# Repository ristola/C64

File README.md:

# C64 Development Workspace

Four related but independent hardware/software projects.

## Projects

- **[`hello/`](hello/README.md)** — SHACKMATE: a working 13-bank EasyFlash BASIC+ extension cartridge for the C64, plus a planned custom flash-based cartridge/expansion-platform PCB that supersedes it, and a Magic Desk-format test build for an already-owned real-hardware bring-up board. The most developed project here; see its own README and `docs/` for full detail.
- **[`eprom-reader/`](eprom-reader/README.md)** — reads 27C64 through 27C512 EPROMs and stores the dump to disk. Scaffolding only, no design work started.
- **[`eeprom-writer/`](eeprom-writer/README.md)** — loads a 27CXX ROM binary and writes it to 27SF256-series EEPROMs. Scaffolding only, no design work started.
- **[`programmer-cartridge/`](programmer-cartridge/README.md)** — a C64 cartridge that programs other cartridges: a ZIF socket for loose EPROM/EEPROM chips plus a second socket for in-circuit programming a companion barebones (surface-mount, non-socketed) release cartridge, with all read/write/backup/clone/load tooling running on the C64 itself. Concept stage, no design work started.

## Why these are grouped together

`eprom-reader/`, `eeprom-writer/`, and `programmer-cartridge/` all exist to support hardware bring-up and eventual distribution for `hello/`'s planned custom board and its release cartridges — dumping/archiving existing EPROM-based cartridges, burning built ROM images during development, and (via `programmer-cartridge/`) eventually producing cheap, mass-producible release hardware. They're independent projects (own toolchains, own hardware, own timelines) but share that practical relationship, and `programmer-cartridge/`'s on-device software overlaps directly with `hello/`'s stubbed Bank 9 (`FLASHERASE`/`FLASHLOAD`/`FLASHVERIFY`) — the same flash erase/write/verify sequence serves both.

`EasyFlash-AppSupport.pdf` / `EasyFlash-ProgRef.pdf` are the real EasyFlash reference docs, kept here for cross-checking `hello/`'s hardware-platform design (GAME/EXROM behavior, register semantics) against something authoritative.

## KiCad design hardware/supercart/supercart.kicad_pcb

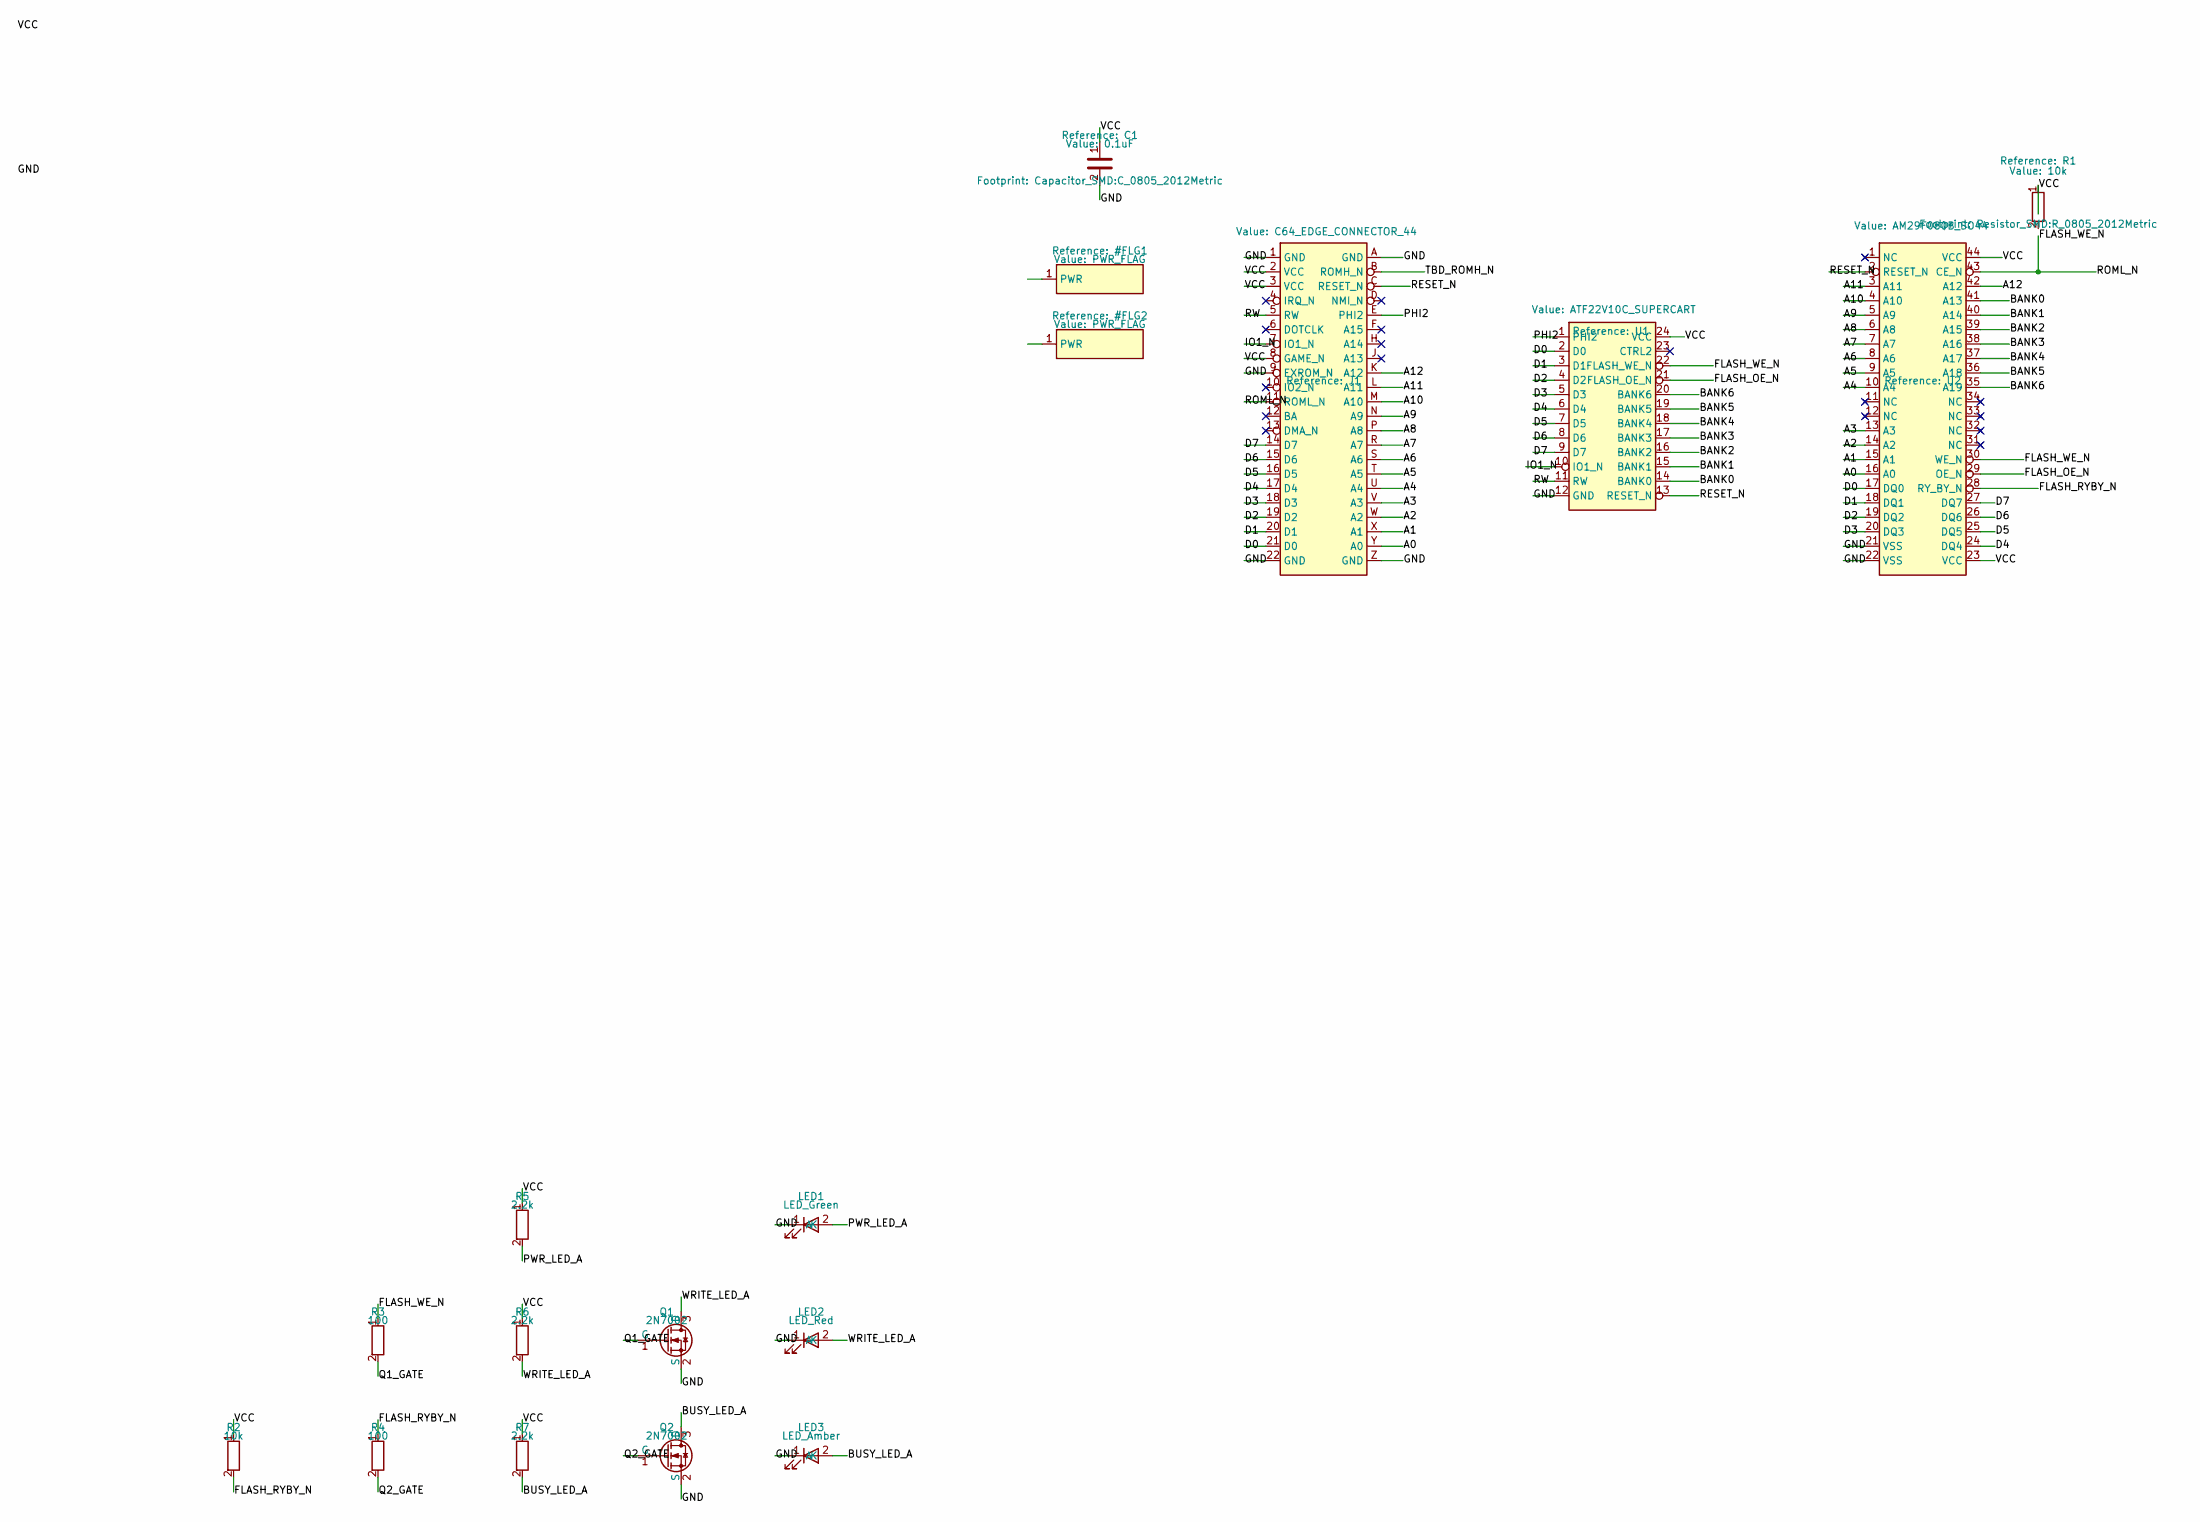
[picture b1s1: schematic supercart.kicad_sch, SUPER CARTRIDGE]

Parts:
C1: 0.1uF; C_0805_2012Metric
J1: C64_EDGE_CONNECTOR_44
LED1: LED_Green; LED_0805_2012Metric
LED2: LED_Red; LED_0805_2012Metric
LED3: LED_Amber; LED_0805_2012Metric
Q1, Q2: 2N7002; SOT-23
R1, R2: 10k; R_0805_2012Metric
R3, R4: 100; R_0805_2012Metric
R5, R6, R7: 2.2k; R_0805_2012Metric
U1: ATF22V10C_SUPERCART
U2: AM29F080B_SO44

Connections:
A0: J1.Y (A0), U2.16 (A0)
A1: J1.X (A1), U2.15 (A1)
A2: J1.W (A2), U2.14 (A2)
A3: J1.V (A3), U2.13 (A3)
A4: J1.U (A4), U2.10 (A4)
A5: J1.T (A5), U2.9 (A5)
A6: J1.S (A6), U2.8 (A6)
A7: J1.R (A7), U2.7 (A7)
A8: J1.P (A8), U2.6 (A8)
A9: J1.N (A9), U2.5 (A9)
A10: J1.M (A10), U2.4 (A10)
A11: J1.L (A11), U2.3 (A11)
A12: J1.K (A12), U2.42 (A12)
BANK0: U1.14 (BANK0), U2.41 (A13)
BANK1: U1.15 (BANK1), U2.40 (A14)
BANK2: U1.16 (BANK2), U2.39 (A15)
BANK3: U1.17 (BANK3), U2.38 (A16)
BANK4: U1.18 (BANK4), U2.37 (A17)
BANK5: U1.19 (BANK5), U2.36 (A18)
BANK6: U1.20 (BANK6), U2.35 (A19)
BUSY_LED_A: LED3.2 (A), Q2.3 (D), R7.2
D0: J1.21 (D0), U1.2 (D0), U2.17 (DQ0)
D1: J1.20 (D1), U1.3 (D1), U2.18 (DQ1)
D2: J1.19 (D2), U1.4 (D2), U2.19 (DQ2)
D3: J1.18 (D3), U1.5 (D3), U2.20 (DQ3)
D4: J1.17 (D4), U1.6 (D4), U2.24 (DQ4)
D5: J1.16 (D5), U1.7 (D5), U2.25 (DQ5)
D6: J1.15 (D6), U1.8 (D6), U2.26 (DQ6)
D7: J1.14 (D7), U1.9 (D7), U2.27 (DQ7)
FLASH_OE_N: U1.21 (FLASH_OE_N), U2.29 (OE_N)
FLASH_RYBY_N: R2.2, R4.1, U2.28 (RY_BY_N)
GND: C1.2, J1.1 (GND), J1.9 (EXROM_N), J1.22 (GND), J1.A (GND), J1.Z (GND), LED1.1 (K), LED2.1 (K), LED3.1 (K), Q1.2 (S), Q2.2 (S), U1.12 (GND), U2.21 (VSS), U2.22 (VSS); also elsewhere on the board
IO1_N: J1.7 (IO1_N), U1.10 (IO1_N)
PHI2: J1.E (PHI2), U1.1 (PHI2)
PWR_LED_A: LED1.2 (A), R5.2
Q1_GATE: Q1.1 (G), R3.2
Q2_GATE: Q2.1 (G), R4.2
RESET_N: J1.C (RESET_N), U1.13 (RESET_N), U2.2 (RESET_N)
RW: J1.5 (RW), U1.11 (RW)
TBD_ROMH_N: J1.B (ROMH_N)
VCC: C1.1, J1.2 (VCC), J1.3 (VCC), J1.8 (GAME_N), R1.1, R2.1, R5.1, R6.1, R7.1, U1.24 (VCC), U2.23 (VCC), U2.44 (VCC); also elsewhere on the board
WRITE_LED_A: LED2.2 (A), Q1.3 (D), R6.2

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
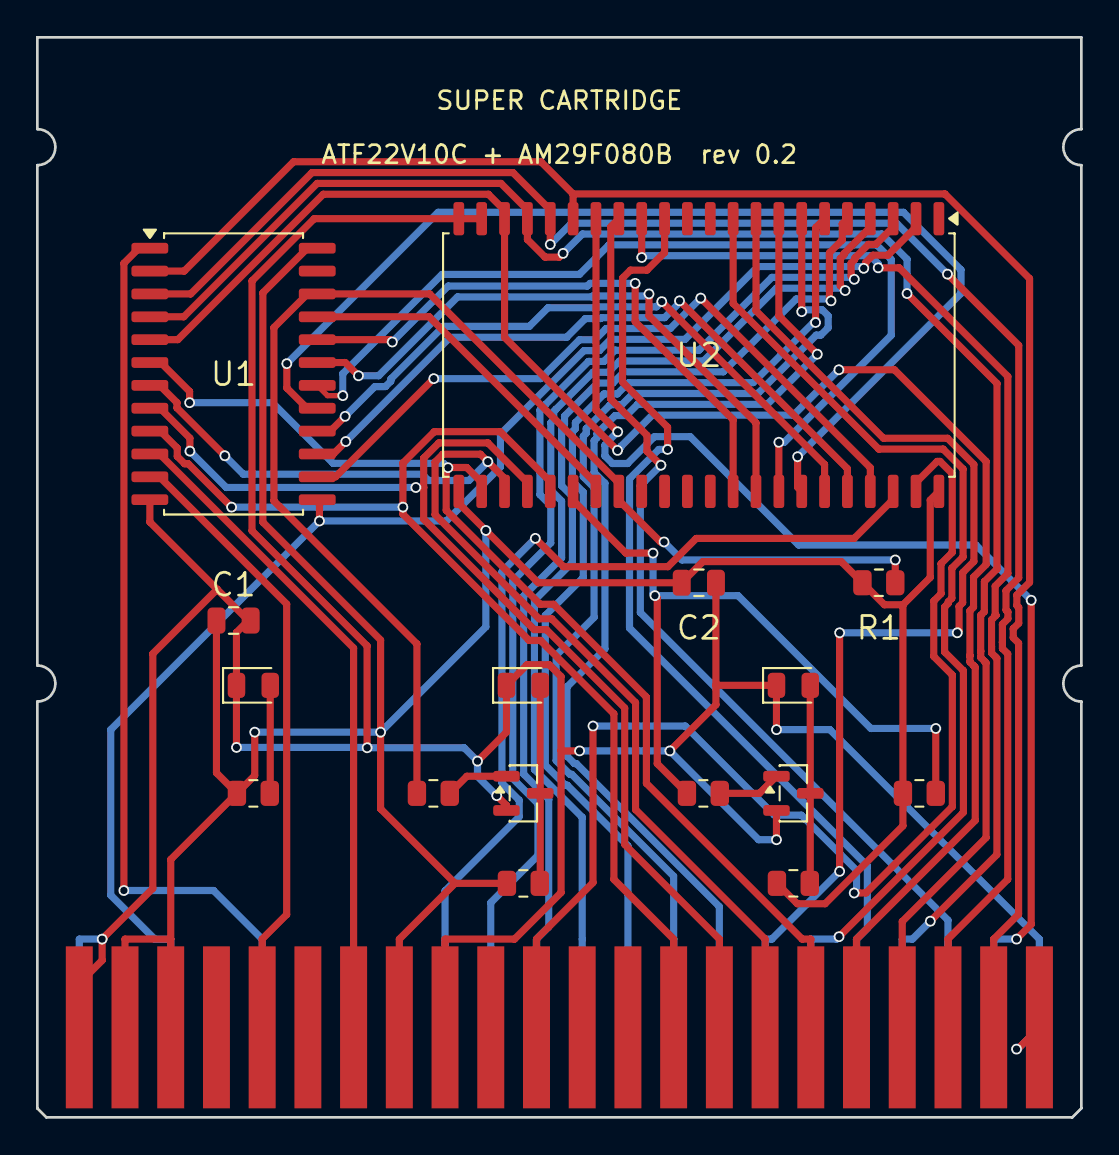
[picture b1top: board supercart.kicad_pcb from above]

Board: 2 copper layers, 58.0 x 60.0 mm, 18 parts (1 on the bottom side), 43 nets.

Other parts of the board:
C2: 0.1uF; C_0805_2012Metric
LOGO1: ShackMate; SHACKMATE_LOGO

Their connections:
GND: C2.2; also elsewhere on the board
VCC: C2.1; also elsewhere on the board

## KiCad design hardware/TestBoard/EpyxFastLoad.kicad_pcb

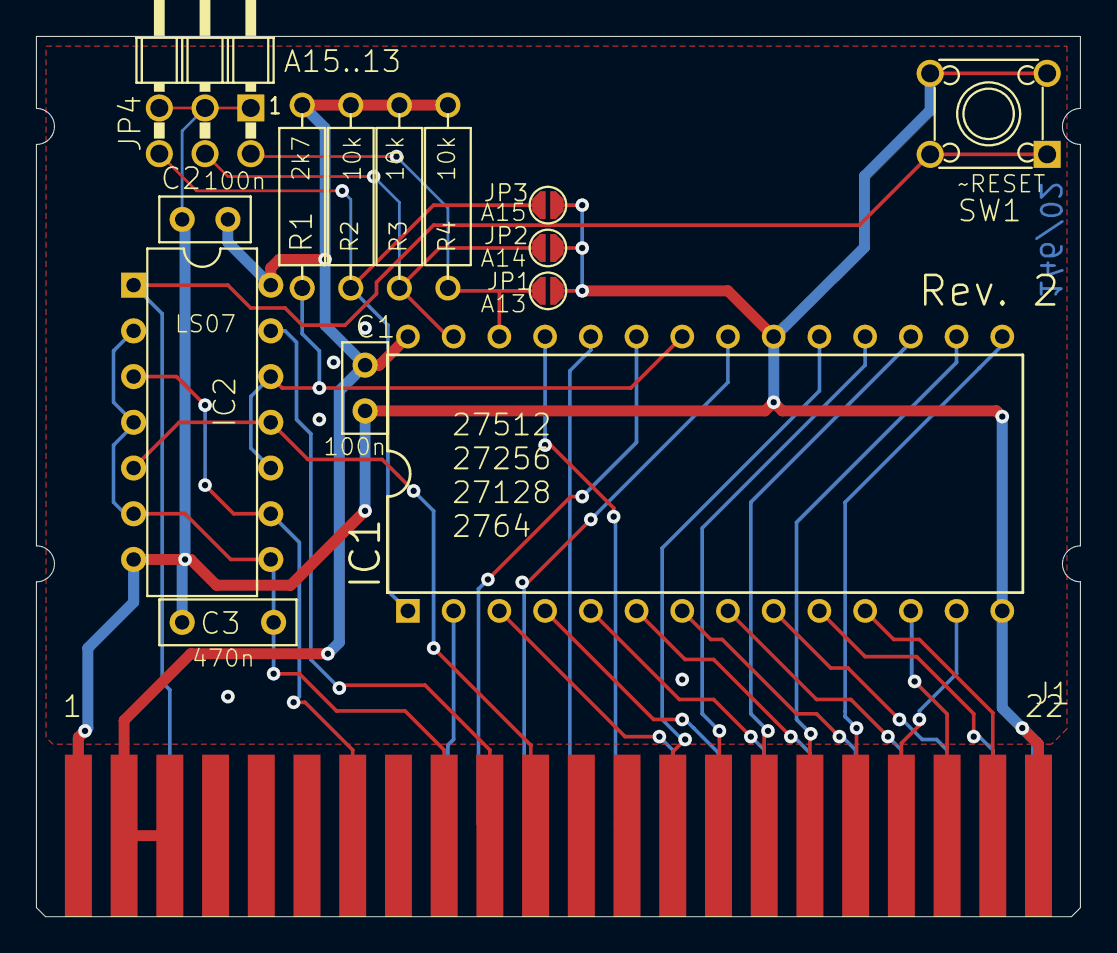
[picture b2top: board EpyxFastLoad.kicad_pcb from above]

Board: 2 copper layers, 58.0 x 48.9 mm, 16 parts (1 on the bottom side), 32 nets.

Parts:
C1, C2: 100n; C-2,5
C3: 470n; C-5
IC1: 27C512-DIP28; DIL28-6
IC2: SN74LS07N; DIL-14
J1: C64-EXPANSION-PORT; EXPANSIO_SQ
JP1, JP2, JP3: OPEN; CP_OP
JP4: PINHD-2X390°; 2X03_90_SERIES_088
R1: 2k7; R-10
R2, R3, R4: 10k; R-10
SW1: JTP-1130
U$39: OPEN_SOURCE_HW; OPENHW

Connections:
+5V: C1.2, C2.2, IC1.28 (VCC), IC2.14 (VCC), J1.2 (+5V), J1.3 (+5V), R1.2, R2.2, R3.2, R4.2
A0: IC1.10 (A0), J1.Y (A0)
A1: IC1.9 (A1), J1.X (A1)
A2: IC1.8 (A2), J1.W (A2)
A3: IC1.7 (A3), J1.V (A3)
A4: IC1.6 (A4), J1.U (A4)
A5: IC1.5 (A5), J1.T (A5)
A6: IC1.4 (A6), J1.S (A6)
A7: IC1.3 (A7), J1.R (A7)
A8: IC1.25 (A8), J1.P (A8)
A9: IC1.24 (A9), J1.N (A9)
A10: IC1.21 (A10), J1.M (A10)
A11: IC1.23 (A11), J1.L (A11)
A12: IC1.2 (A12), J1.K (A12)
A13: IC1.26 (A13), JP1.2, JP4.2, R4.1
A14: IC1.27 (A14), JP2.2, JP4.4, R3.1
A15: IC1.1 (A15), JP3.2, JP4.6, R2.1
D0: IC1.11 (D0), J1.21 (D0)
D1: IC1.12 (D1), J1.20 (D1)
D2: IC1.13 (D2), J1.19 (D2)
D3: IC1.15 (D3), J1.18 (D3)
D4: IC1.16 (D4), J1.17 (D4)
D5: IC1.17 (D5), J1.16 (D5)
D6: IC1.18 (D6), J1.15 (D6)
D7: IC1.19 (D7), J1.14 (D7)
GND: C1.1, C2.1, C3.2, IC1.14 (VSS), IC1.20 (~E), IC2.7 (GND), J1.1 (GND), J1.22 (GND), J1.A (GND), J1.Z (GND), JP1.1, JP2.1, JP3.1, JP4.1, JP4.3, JP4.5, SW1.3, SW1.4
~EXROM: C3.1, IC2.2 (O), IC2.4 (O), IC2.6 (O), IC2.8 (O), J1.9 (~EXROM)
~I/O1: IC2.3 (I), IC2.9 (I), J1.7 (~I/O1)
~I/O2: IC2.13 (I), J1.10 (~I/O2)
~OE: IC1.22 (~GVPP), IC2.10 (O), IC2.12 (O), R1.1
~RESET: IC2.1 (I), J1.C (~RESET), SW1.1, SW1.2
~ROML: IC2.5 (I), IC2.11 (I), J1.11 (~ROML)
